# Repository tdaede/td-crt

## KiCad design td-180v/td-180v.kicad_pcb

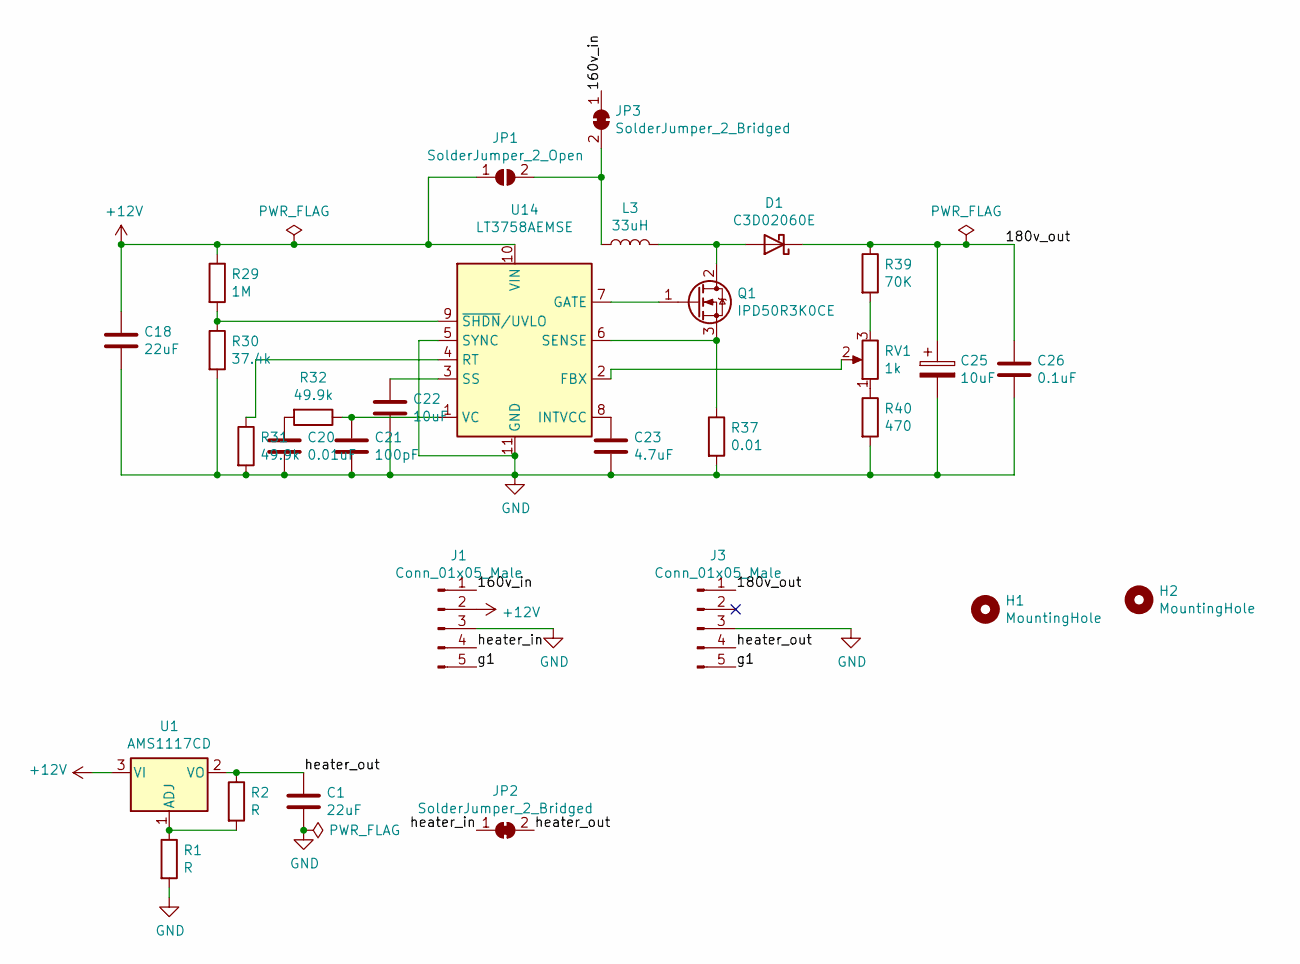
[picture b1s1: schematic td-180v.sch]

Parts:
C1, C18: 22uF; CP_Radial_D8.0mm_P3.50mm; Voltage 63V; Digikey 493-3872-1-ND
C20: 0.01uF; C_0805_2012Metric_Pad1.18x1.45mm_HandSolder; Voltage 10V; Digikey 1276-2434-1-ND
C21: 100pF; C_0805_2012Metric_Pad1.18x1.45mm_HandSolder; Voltage 10V; Digikey 1276-2569-1-ND
C22: 10uF; C_1206_3216Metric_Pad1.33x1.80mm_HandSolder; Voltage 10V; Digikey 1276-6641-1-ND
C23: 4.7uF; C_0805_2012Metric_Pad1.18x1.45mm_HandSolder; Voltage 10V; Digikey 1276-3177-1-ND
C25: 10uF; CP_Radial_D8.0mm_P3.50mm; Voltage 200V; Digikey UVK2D100MPD-ND
C26: 0.1uF; C_1206_3216Metric_Pad1.33x1.80mm_HandSolder; Voltage 200V; Digikey 1276-3084-1-ND
D1: C3D02060E; TO-252-2_TabPin1
H1, H2: MountingHole; MountingHole_3.2mm_M3
J1: Conn_01x05_Male; JST_XH_S5B-XH-A_1x05_P2.50mm_Horizontal
J3: Conn_01x05_Male; JST_XH_B5B-XH-A_1x05_P2.50mm_Vertical
JP1: SolderJumper_2_Open; SolderJumper-2_P1.3mm_Open_Pad1.0x1.5mm
JP2, JP3: SolderJumper_2_Bridged; SolderJumper-2_P1.3mm_Bridged_Pad1.0x1.5mm
L3: 33uH; L_Taiyo-Yuden_NR-60xx_HandSoldering; Digikey 587-2631-1-ND
Q1: IPD50R3K0CE; TO-252-2
R1, R2: R; R_0805_2012Metric_Pad1.20x1.40mm_HandSolder
R29: 1M; R_0805_2012Metric_Pad1.20x1.40mm_HandSolder; Digikey 311-1.00MCRCT-ND
R30: 37.4k; R_0805_2012Metric_Pad1.20x1.40mm_HandSolder; Digikey 311-37.4KCRCT-ND
R31, R32: 49.9k; R_0805_2012Metric_Pad1.20x1.40mm_HandSolder; Digikey 311-49.9KCRCT-ND
R37: 0.01; R_0805_2012Metric_Pad1.20x1.40mm_HandSolder; Digikey 311-0.01NUCT-ND
R39: 70K; R_0805_2012Metric_Pad1.20x1.40mm_HandSolder; Digikey 311-68.0KFRCT-ND
R40: 470; R_0805_2012Metric_Pad1.20x1.40mm_HandSolder; Digikey 311-470CRCT-ND
RV1: 1k; Potentiometer_Bourns_3386P_Vertical; Digikey 3386P-102LF-ND
U1: AMS1117CD; TO-252-3_TabPin2
U14: LT3758AEMSE; MSOP-10-1EP_3x3mm_P0.5mm_EP1.68x1.88mm; Digikey LT3758AEMSE#TRPBFCT-ND

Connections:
+12V: C18.1, J1.2, JP1.1 (A), R29.1, U1.3 (VI), U14.10 (VIN)
/160v_in: J1.1, JP3.1 (A)
/180v_out: C25.1, C26.1, D1.1 (K), J3.1, R39.1
/g1: J1.5, J3.5
/heater_in: J1.4, JP2.1 (A)
/heater_out: C1.1, J3.4, JP2.2 (B), R2.1, U1.2 (VO)
GND: C1.2, C18.2, C20.2, C21.2, C22.2, C23.2, C25.2, C26.2, J1.3, J3.3, R1.2, R30.2, R31.2, R37.2, R40.2, U14.5 (SYNC), U14.11 (GND)
unnamed: C20.1, R32.2
unnamed: C21.1, R32.1, U14.1 (VC)
unnamed: C22.1, U14.3 (SS)
unnamed: C23.1, U14.8 (INTVCC)
unnamed: D1.2 (A), L3.2, Q1.2 (D)
unnamed: JP1.2 (B), JP3.2 (B), L3.1
unnamed: Q1.1 (G), U14.7 (GATE)
unnamed: Q1.3 (S), R37.1, U14.6 (SENSE)
unnamed: R1.1, R2.2, U1.1 (ADJ)
unnamed: R29.2, R30.1, U14.9 (~SHDN~/UVLO)
unnamed: R31.1, U14.4 (RT)
unnamed: R39.2, RV1.3
unnamed: R40.1, RV1.1
unnamed: RV1.2, U14.2 (FBX)

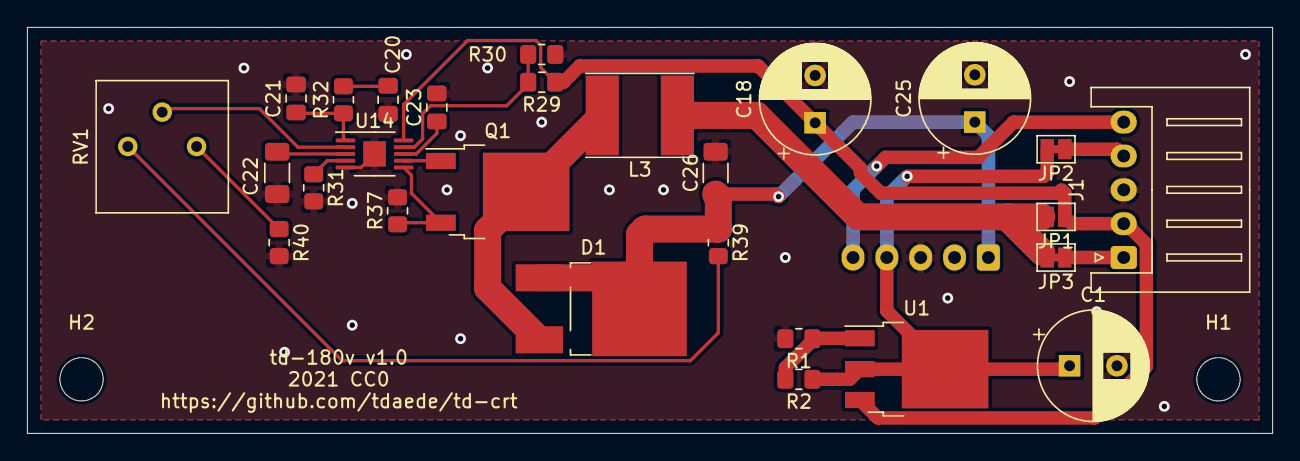
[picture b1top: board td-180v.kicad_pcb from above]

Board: 2 copper layers, 92.0 x 30.0 mm, 30 parts (1 on the bottom side), 21 nets.

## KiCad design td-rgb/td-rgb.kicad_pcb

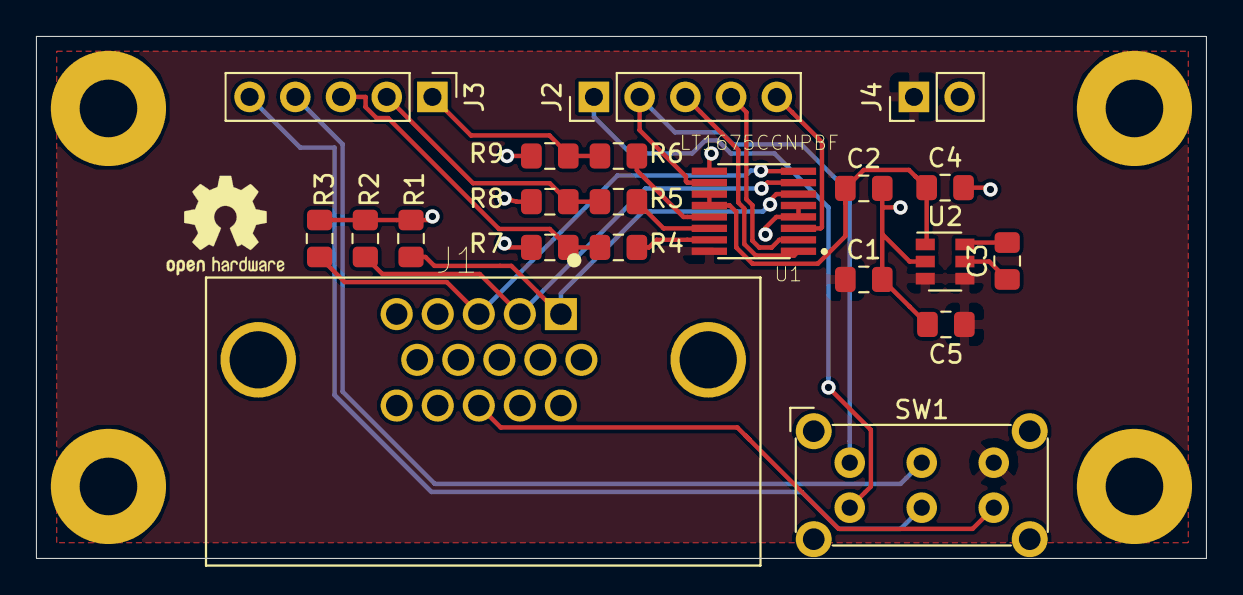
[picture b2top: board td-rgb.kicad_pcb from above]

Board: 2 copper layers, 65.0 x 29.0 mm, 21 parts (0 on the bottom side), 22 nets.

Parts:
C1, C2: C; C_0805_2012Metric_Pad1.15x1.40mm_HandSolder
C3: 1uF; C_0805_2012Metric_Pad1.15x1.40mm_HandSolder
C4, C5: 2.2uF; C_0805_2012Metric_Pad1.15x1.40mm_HandSolder
J1: ICD15S13E4GV00LF; TE_1-1734530-1
J2, J3: Conn_01x05_Male; PinHeader_1x05_P2.54mm_Vertical
J4: Conn_01x02_Male; PinHeader_1x02_P2.54mm_Vertical
R1, R2, R3, R4, R5, R6, R7, R8, R9: 75; R_0805_2012Metric_Pad1.15x1.40mm_HandSolder
SW1: SW_DPDT_x2; SW_E-Switch_EG2219_DPDT_Angled
U1: LT1675CGNPBF; SOP63P600X172-16N
U2: LM2776; SOT-23-6

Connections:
+5V: C1.1, C5.1, J4.1, SW1.3, U1.16, U2.3, U2.4
-5V: C2.1, C4.1, U1.11, U1.12, U2.1
/blank_in: J2.2, SW1.1, U1.10
/blue: J1.3, R3.1, U1.8
/blue_in: J2.5, U1.3
/blue_out: J3.1, R6.1, R9.1
/csync_out: J3.5, SW1.5
/green: J1.2, R2.1, U1.7
/green_in: J2.4, U1.2
/green_out: J3.2, R5.1, R8.1
/red: J1.1, R1.1, U1.6
/red_in: J2.3, U1.1
/red_out: J3.3, R4.1, R7.1
GND: C1.2, C2.2, C4.2, C5.2, J1.5, J1.6, J1.7, J1.8, J4.2, R1.2, R2.2, R3.2, R7.2, R8.2, R9.2, U1.4, U1.5, U1.9, U2.2
unnamed: C3.1, U2.5
unnamed: C3.2, U2.6
unnamed: J1.13, SW1.6
unnamed: J2.1, SW1.4
unnamed: J3.4, SW1.2
unnamed: R4.2, U1.15
unnamed: R5.2, U1.14
unnamed: R6.2, U1.13

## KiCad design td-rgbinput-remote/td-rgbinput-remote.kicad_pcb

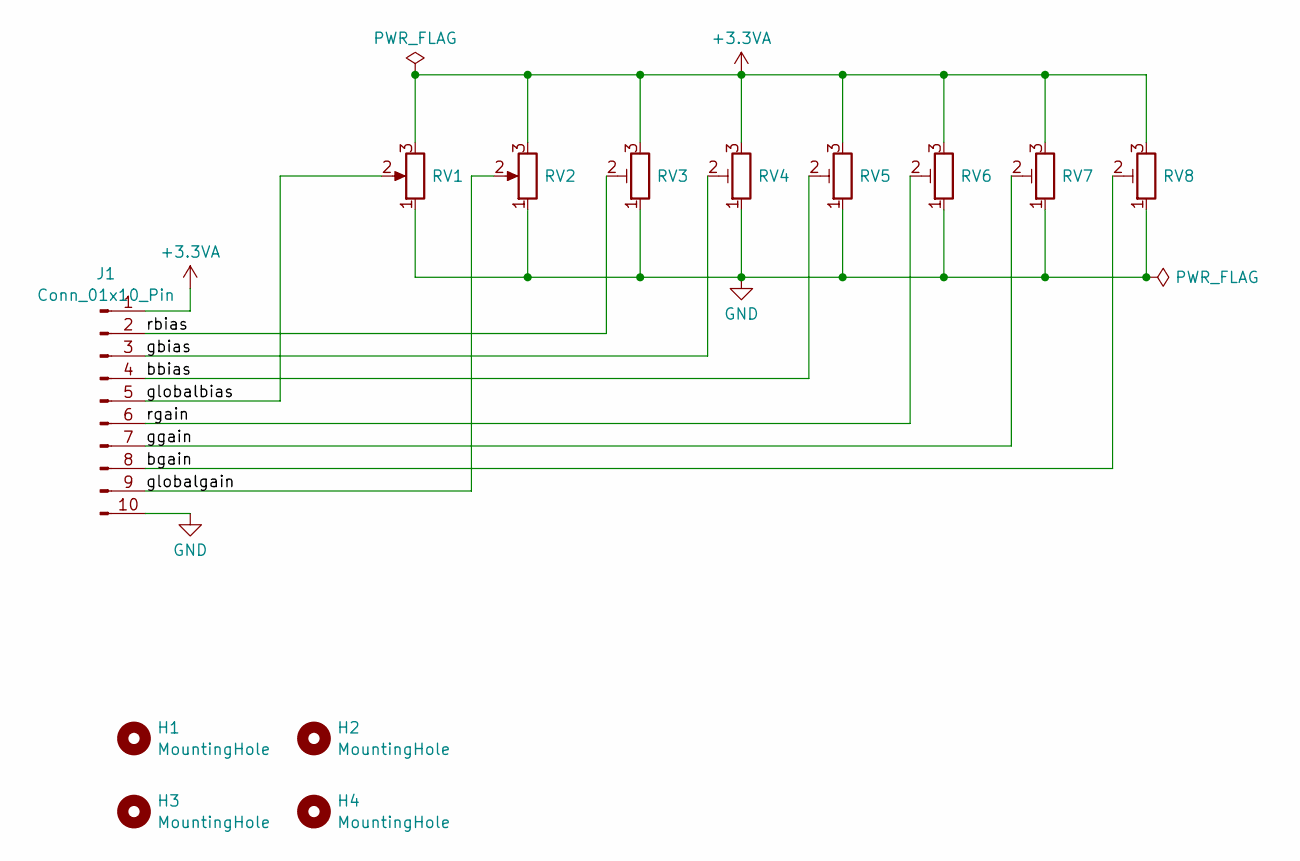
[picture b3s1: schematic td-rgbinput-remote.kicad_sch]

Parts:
H1, H2, H3, H4: MountingHole; MountingHole_3.2mm_M3
J1: Conn_01x10_Pin; JST_XH_S10B-XH-A_1x10_P2.50mm_Horizontal; Digikey 455-S10B-XH-A-ND
RV1, RV2: R_Potentiometer; Potentiometer_Alps_RK09K_Single_Vertical; Digikey CT3182-ND
RV3, RV4, RV5, RV6, RV7, RV8: R_Potentiometer_Trim; Potentiometer_Bourns_3386P_Vertical; Digikey 3386P-103TLF-ND

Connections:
+3.3VA: J1.1, RV1.3, RV2.3, RV3.3, RV4.3, RV5.3, RV6.3, RV7.3, RV8.3
/bbias: J1.4, RV5.2
/bgain: J1.8, RV8.2
/gbias: J1.3, RV4.2
/ggain: J1.7, RV7.2
/globalbias: J1.5, RV1.2
/globalgain: J1.9, RV2.2
/rbias: J1.2, RV3.2
/rgain: J1.6, RV6.2
GND: J1.10, RV1.1, RV2.1, RV3.1, RV4.1, RV5.1, RV6.1, RV7.1, RV8.1

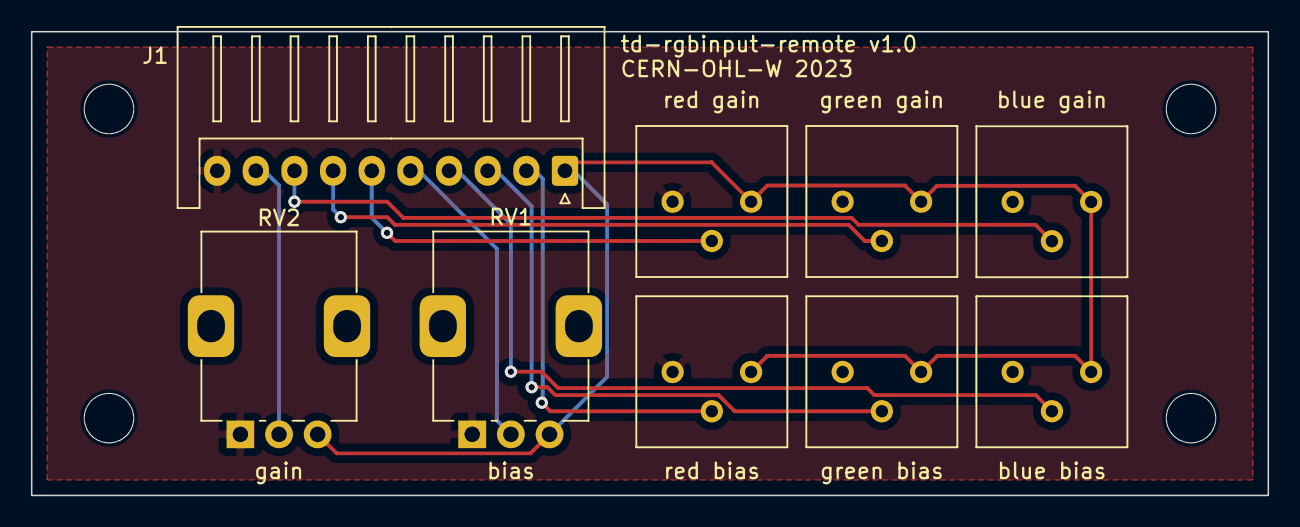
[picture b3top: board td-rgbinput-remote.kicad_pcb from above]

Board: 2 copper layers, 80.0 x 30.0 mm, 13 parts (0 on the bottom side), 10 nets.

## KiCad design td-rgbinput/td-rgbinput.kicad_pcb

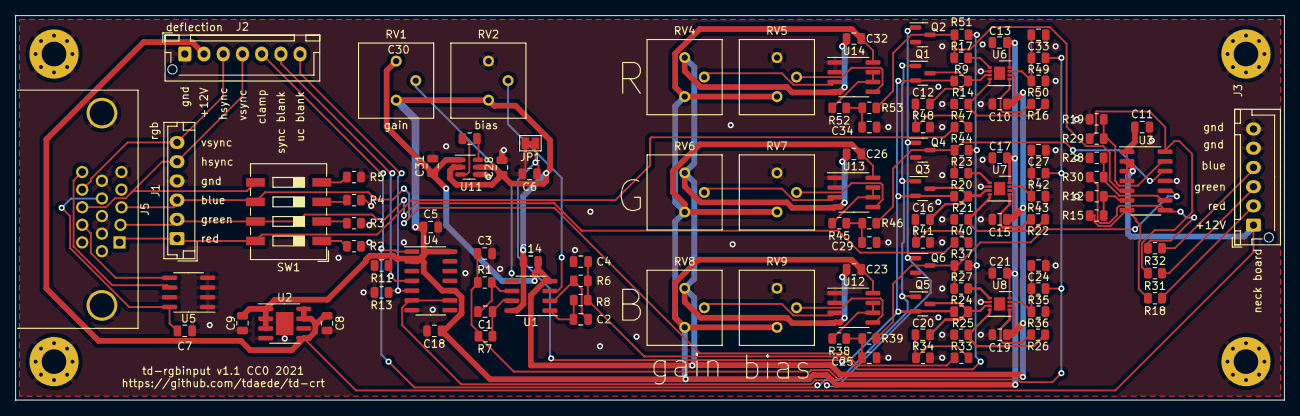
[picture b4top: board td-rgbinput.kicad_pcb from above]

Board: 2 copper layers, 165.0 x 50.0 mm, 121 parts (0 on the bottom side), 73 nets.

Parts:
C1, C2: 0.01uF; C_0805_2012Metric
C3, C4, C5, C6, C7, C10, C11, C13, C14, C15, C17, C18, C19, C21, C23, C24, C25, C26, C27, C29, C32, C33, C34: 0.1uF; C_0805_2012Metric
C8, C9: 2.2uF; C_0805_2012Metric
C12, C16, C20: 1uF; C_0805_2012Metric
C28, C30, C31: 3.3uF; C_0805_2012Metric
H1, H2, H3, H4: MountingHole_Pad; MountingHole_3.2mm_M3_Pad_Via
J1: Conn_01x06_Male; JST_EH_B6B-EH-A_1x06_P2.50mm_Vertical
J2: Conn_01x07_Male; JST_XH_B7B-XH-AM_1x07_P2.50mm_Vertical
J3: Conn_01x06_Male; JST_XH_B6B-XH-AM_1x06_P2.50mm_Vertical
J5: DB15_Female_HighDensity_MountingHoles; DSUB-15-HD_Female_Horizontal_P2.29x2.5mm_EdgePinOffset8.35m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
JP1: Jumper_NC_Small; SolderJumper-2_P1.3mm_Bridged_Pad1.0x1.5mm
Q1, Q2, Q3, Q4, Q5, Q6: 2N7002NXBKR; SOT-23
R1, R6, R17, R23, R27, R33, R34, R35, R36, R37, R39, R40, R41, R42, R43, R44, R46, R47, R48, R49, R50, R51, R53: 1k; R_0805_2012Metric
R2, R3, R4, R5: 75; R_0805_2012Metric
R7, R8, R38, R45, R52: 10; R_0805_2012Metric
R9, R20, R24: 100k; R_0805_2012Metric
R11, R13: 10k; R_0805_2012Metric
R12, R14, R15, R16, R19, R21, R22, R25, R26, R28, R29, R30: 470; R_0805_2012Metric
R18, R31, R32: 47; R_0805_2012Metric
RV1, RV2, RV4, RV5, RV6, RV7, RV8, RV9: 1k; Potentiometer_Bourns_3386P_Vertical
SW1: SW_DIP_x04; SW_DIP_SPSTx04_Slide_9.78x12.34mm_W8.61mm_P2.54mm
U1, U12, U13, U14: TLC272; SOIC-8_3.9x4.9mm_P1.27mm
U2: ADP7142ARDZ-5.0; SOIC-8-1EP_3.9x4.9mm_P1.27mm_EP2.29x3mm
U3: ADA4861-3; SOIC-14_3.9x8.7mm_P1.27mm
U4: 74HCT00; SOIC-14_3.9x8.7mm_P1.27mm
U5: AT24CS01-SSHM; SOIC-8_3.9x4.9mm_P1.27mm
U6, U7, U8: AD8337; LFCSP-8-1EP_3x3mm_P0.5mm_AD8337
U11: MAX1720EUT; SOT-23-6

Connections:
+5V: C5.1, C9.1, C13.1, C14.1, C17.1, C18.1, C21.1, C23.1, C26.1, C28.1, C32.1, RV1.1, RV2.1, RV4.1, RV5.1, RV6.1, RV7.1, RV8.1, RV9.1, U1.8 (V+), U2.1 (VOUT), U2.2 (VOUT), U2.3 (SENSE/ADJ), U4.2, U4.10, U4.14 (VCC), U6.8 (V+), U7.8 (V+), U8.8 (V+), U11.2 (V+), U11.5 (SHDN), U12.8 (V+), U13.8 (V+), U14.8 (V+)
+12V: C8.1, C11.1, J2.2, J3.1, U2.5 (EN), U2.7 (VIN), U2.8 (VIN), U3.1 (~DISABLE), U3.2 (~DISABLE), U3.3 (~DISABLE), U3.4 (V+)
-5V: C10.1, C14.2, C15.1, C19.1, C23.2, C26.2, C31.1, C32.2, RV1.3, RV4.3, RV6.3, RV8.3, U1.4 (V-), U6.6 (V-), U7.6 (V-), U8.6 (V-), U11.1 (OUT), U12.4 (V-), U13.4 (V-), U14.4 (V-)
/Blue/ac: C20.1, Q5.3 (D), R24.1, U8.3 (+)
/Green/ac: C16.1, Q3.3 (D), R20.1, U7.3 (+)
/Red/ac: C12.1, Q1.3 (D), R9.1, U6.3 (+)
/blue_fb: R28.2, R30.2, U3.9 (-)
/green_fb: R19.2, R29.2, U3.13 (-)
/mixed_blue: Q6.3 (D), R27.1, R37.1, R39.2, U3.10 (+)
/mixed_green: Q4.3 (D), R23.1, R44.1, R46.2, U3.12 (+)
/mixed_red: Q2.3 (D), R17.1, R51.1, R53.2, U3.5 (+)
/neck_blue: J3.4, R32.1
/neck_green: J3.3, R31.1
/neck_red: J3.2, R18.1
/red_fb: R12.2, R15.2, U3.6 (-)
/sync_blank: J2.6, R11.1, U4.4
/uc_blank: J2.7, R13.1, U4.5
/vga_blue: J1.3, J5.3, R33.1, SW1.6
/vga_green: J1.2, J5.2, R40.1, SW1.7
/vga_hsync: J1.5, J2.4, J5.13, SW1.5
/vga_red: J1.1, J5.1, R47.1, SW1.8
/vga_vsync: J1.6, J2.3, J5.14
GND: C3.2, C4.2, C5.2, C6.2, C7.2, C8.2, C9.2, C10.2, C11.2, C13.2, C15.2, C17.2, C18.2, C19.2, C21.2, C24.2, C25.2, C27.2, C28.2, C29.2, C31.2, C33.2, C34.2, H1.1, H2.1, H3.1, H4.1, J1.4, J2.1, J3.5, J3.6, J5.0, J5.5, J5.6, J5.7, J5.8, J5.10, JP1.2, Q2.2 (S), Q4.2 (S), Q6.2 (S), R2.2, R3.2, R4.2, R5.2, R11.2, R12.1, R13.2, R14.1, R19.1, R21.1, R25.1, R28.1, R34.2, R36.1, R41.2, R43.1, R48.2, R50.1, RV2.3, RV5.3, RV7.3, RV9.3, U2.4 (GND), U2.9 (GND), U3.11 (V-), U4.7 (GND), U5.1 (A0), U5.2 (A1), U5.3 (A2), U5.4 (GND), U5.7 (WP), U6.2 (VCOM), U7.2 (VCOM), U8.2 (VCOM), U11.4 (GND), U12.1, U12.2 (-), U13.1, U13.2 (-), U14.1, U14.2 (-)
unnamed: C1.1, R7.2, U1.7
unnamed: C1.2, R1.2, U1.6 (-)
unnamed: C2.1, R8.2, U1.1
unnamed: C2.2, R6.2, U1.2 (-)
unnamed: C7.1, J5.9, U5.8 (VCC)
unnamed: C12.2, R47.2, R48.1
unnamed: C16.2, R40.2, R41.1
unnamed: C20.2, R33.2, R34.1
unnamed: C25.1, R38.1, R39.1
unnamed: C29.1, R45.1, R46.1
unnamed: C30.1, U11.6 (CAP+)
unnamed: C30.2, U11.3 (CAP-)
unnamed: C34.1, R52.1, R53.1
unnamed: J5.12, U5.5 (SDA)
unnamed: J5.15, U5.6 (SCL)
unnamed: R2.1, SW1.1
unnamed: R3.1, SW1.2
unnamed: R4.1, SW1.3
unnamed: R5.1, SW1.4
unnamed: R14.2, R16.2, U6.4 (-)
unnamed: R15.1, R18.2, U3.7
unnamed: R16.1, U6.5 (PRAO)
unnamed: R17.2, U6.1
unnamed: R21.2, R22.2, U7.4 (-)
unnamed: R22.1, U7.5 (PRAO)
unnamed: R23.2, U7.1
unnamed: R25.2, R26.2, U8.4 (-)
unnamed: R26.1, U8.5 (PRAO)
unnamed: R27.2, U8.1
unnamed: R29.1, R31.2, U3.14
unnamed: R30.1, R32.2, U3.8
unnamed: R38.2, U12.6 (-), U12.7
unnamed: R45.2, U13.6 (-), U13.7
unnamed: R52.2, U14.6 (-), U14.7
unnamed: RV1.2, U1.5 (+)
unnamed: RV2.2, U1.3 (+)
unnamed: RV4.2, U14.3 (+)
unnamed: RV5.2, U14.5 (+)
unnamed: RV6.2, U13.3 (+)
unnamed: RV7.2, U13.5 (+)
unnamed: RV8.2, U12.3 (+)
unnamed: RV9.2, U12.5 (+)
unnamed: C33.1, R49.1, R50.2, U6.7 (GAIN)
unnamed: C27.1, R42.1, R43.2, U7.7 (GAIN)
unnamed: C24.1, R35.1, R36.2, U8.7 (GAIN)
bias_buffered: C4.1, R6.1, R8.1, R37.2, R44.2, R51.2
black_level: C6.1, JP1.1, Q1.2 (S), Q3.2 (S), Q5.2 (S), R9.2, R20.2, R24.2
blank: Q2.1 (G), Q4.1 (G), Q6.1 (G), U4.6, U4.9
clamp: J2.5, Q1.1 (G), Q3.1 (G), Q5.1 (G), U4.1
gain_buffered: C3.1, R1.1, R7.1, R35.2, R42.2, R49.2

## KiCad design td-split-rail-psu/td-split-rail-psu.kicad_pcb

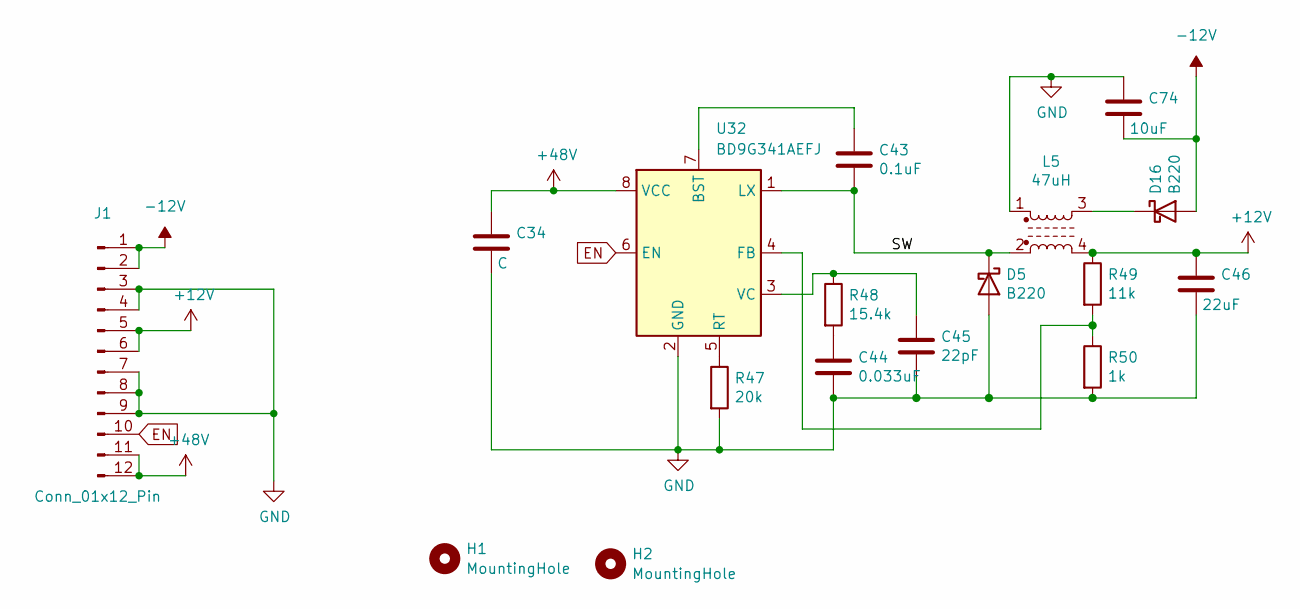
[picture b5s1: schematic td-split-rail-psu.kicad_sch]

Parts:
C34: C; C_1210_3225Metric; Voltage 50V; Digikey 587-1818-1-ND
C43: 0.1uF; C_0805_2012Metric; Voltage 25V; Digikey 1276-1099-1-ND
C44: 0.033uF; C_0805_2012Metric; Voltage 10V; Digikey 311-1374-1-ND
C45: 22pF; C_0805_2012Metric; Digikey 1276-2605-1-ND
C46: 22uF; C_0805_2012Metric; Voltage 16V; Digikey 490-9956-1-ND
C74: 10uF; C_0805_2012Metric; Voltage 16V; Digikey 490-9956-1-ND
D5, D16: B220; D_SMB; Digikey B220A-FDICT-ND
H1, H2: MountingHole; MountingHole_2.5mm
J1: Conn_01x12_Pin; PinHeader_1x12_P2.54mm_Horizontal; Digikey 609-3323-ND
L5: 47uH; L_Bourns_SRF1260; Digikey SRF1260-470MCT-ND
R47: 20k; R_0805_2012Metric; Digikey 311-20.0KCRCT-ND
R48: 15.4k; R_0805_2012Metric; Digikey 311-15.4KCRCT-ND
R49: 11k; R_0805_2012Metric; Digikey 311-11.0KCRCT-ND
R50: 1k; R_0805_2012Metric; Digikey 311-1.00KCRCT-ND
U32: BD9G341AEFJ; SOIC-8-1EP_3.9x4.9mm_P1.27mm_EP2.41x3.3mm_ThermalVias; Digikey BD9G341AEFJ-E2CT-ND

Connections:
+12V: C46.1, J1.5, J1.6, L5.4, R49.1
+48V: C34.1, J1.11, J1.12, U32.8 (VCC)
-12V: C74.2, D16.2 (A), J1.1, J1.2
/SW: C43.2, D5.1 (K), L5.2, U32.1 (LX)
EN: J1.10, U32.6 (EN)
GND: C34.2, C44.2, C45.2, C46.2, C74.1, D5.2 (A), J1.3, J1.4, J1.7, J1.8, J1.9, L5.1, R47.2, R50.2, U32.2 (GND), U32.9 (GND)
unnamed: C44.1, R48.2
unnamed: D16.1 (K), L5.3
unnamed: C43.1, U32.7 (BST)
unnamed: R49.2, R50.1, U32.4 (FB)
unnamed: R47.1, U32.5 (RT)
unnamed: C45.1, R48.1, U32.3 (VC)

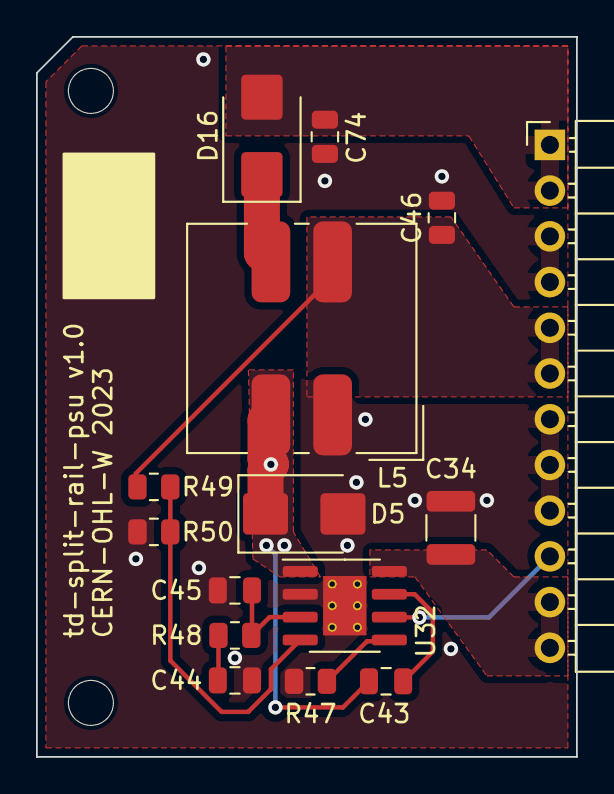
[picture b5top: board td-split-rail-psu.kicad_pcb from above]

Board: 2 copper layers, 30.0 x 40.0 mm, 17 parts (0 on the bottom side), 12 nets.

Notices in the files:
td-180v/td-180v.kicad_pcb:
2021 CC0
td-rgb/td-rgb.kicad_pcb:
td-rgb v1.0 CC0
td-rgbinput-remote/td-rgbinput-remote.kicad_pcb:
CERN-OHL-W 2023
td-rgbinput/td-rgbinput.kicad_pcb:
td-rgbinput v1.1 CC0 2021
